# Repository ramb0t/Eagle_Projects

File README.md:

# Eagle_Projects

A Place to keep my older Eagle Projects from Dropbox... Some noob, Most unfinished.

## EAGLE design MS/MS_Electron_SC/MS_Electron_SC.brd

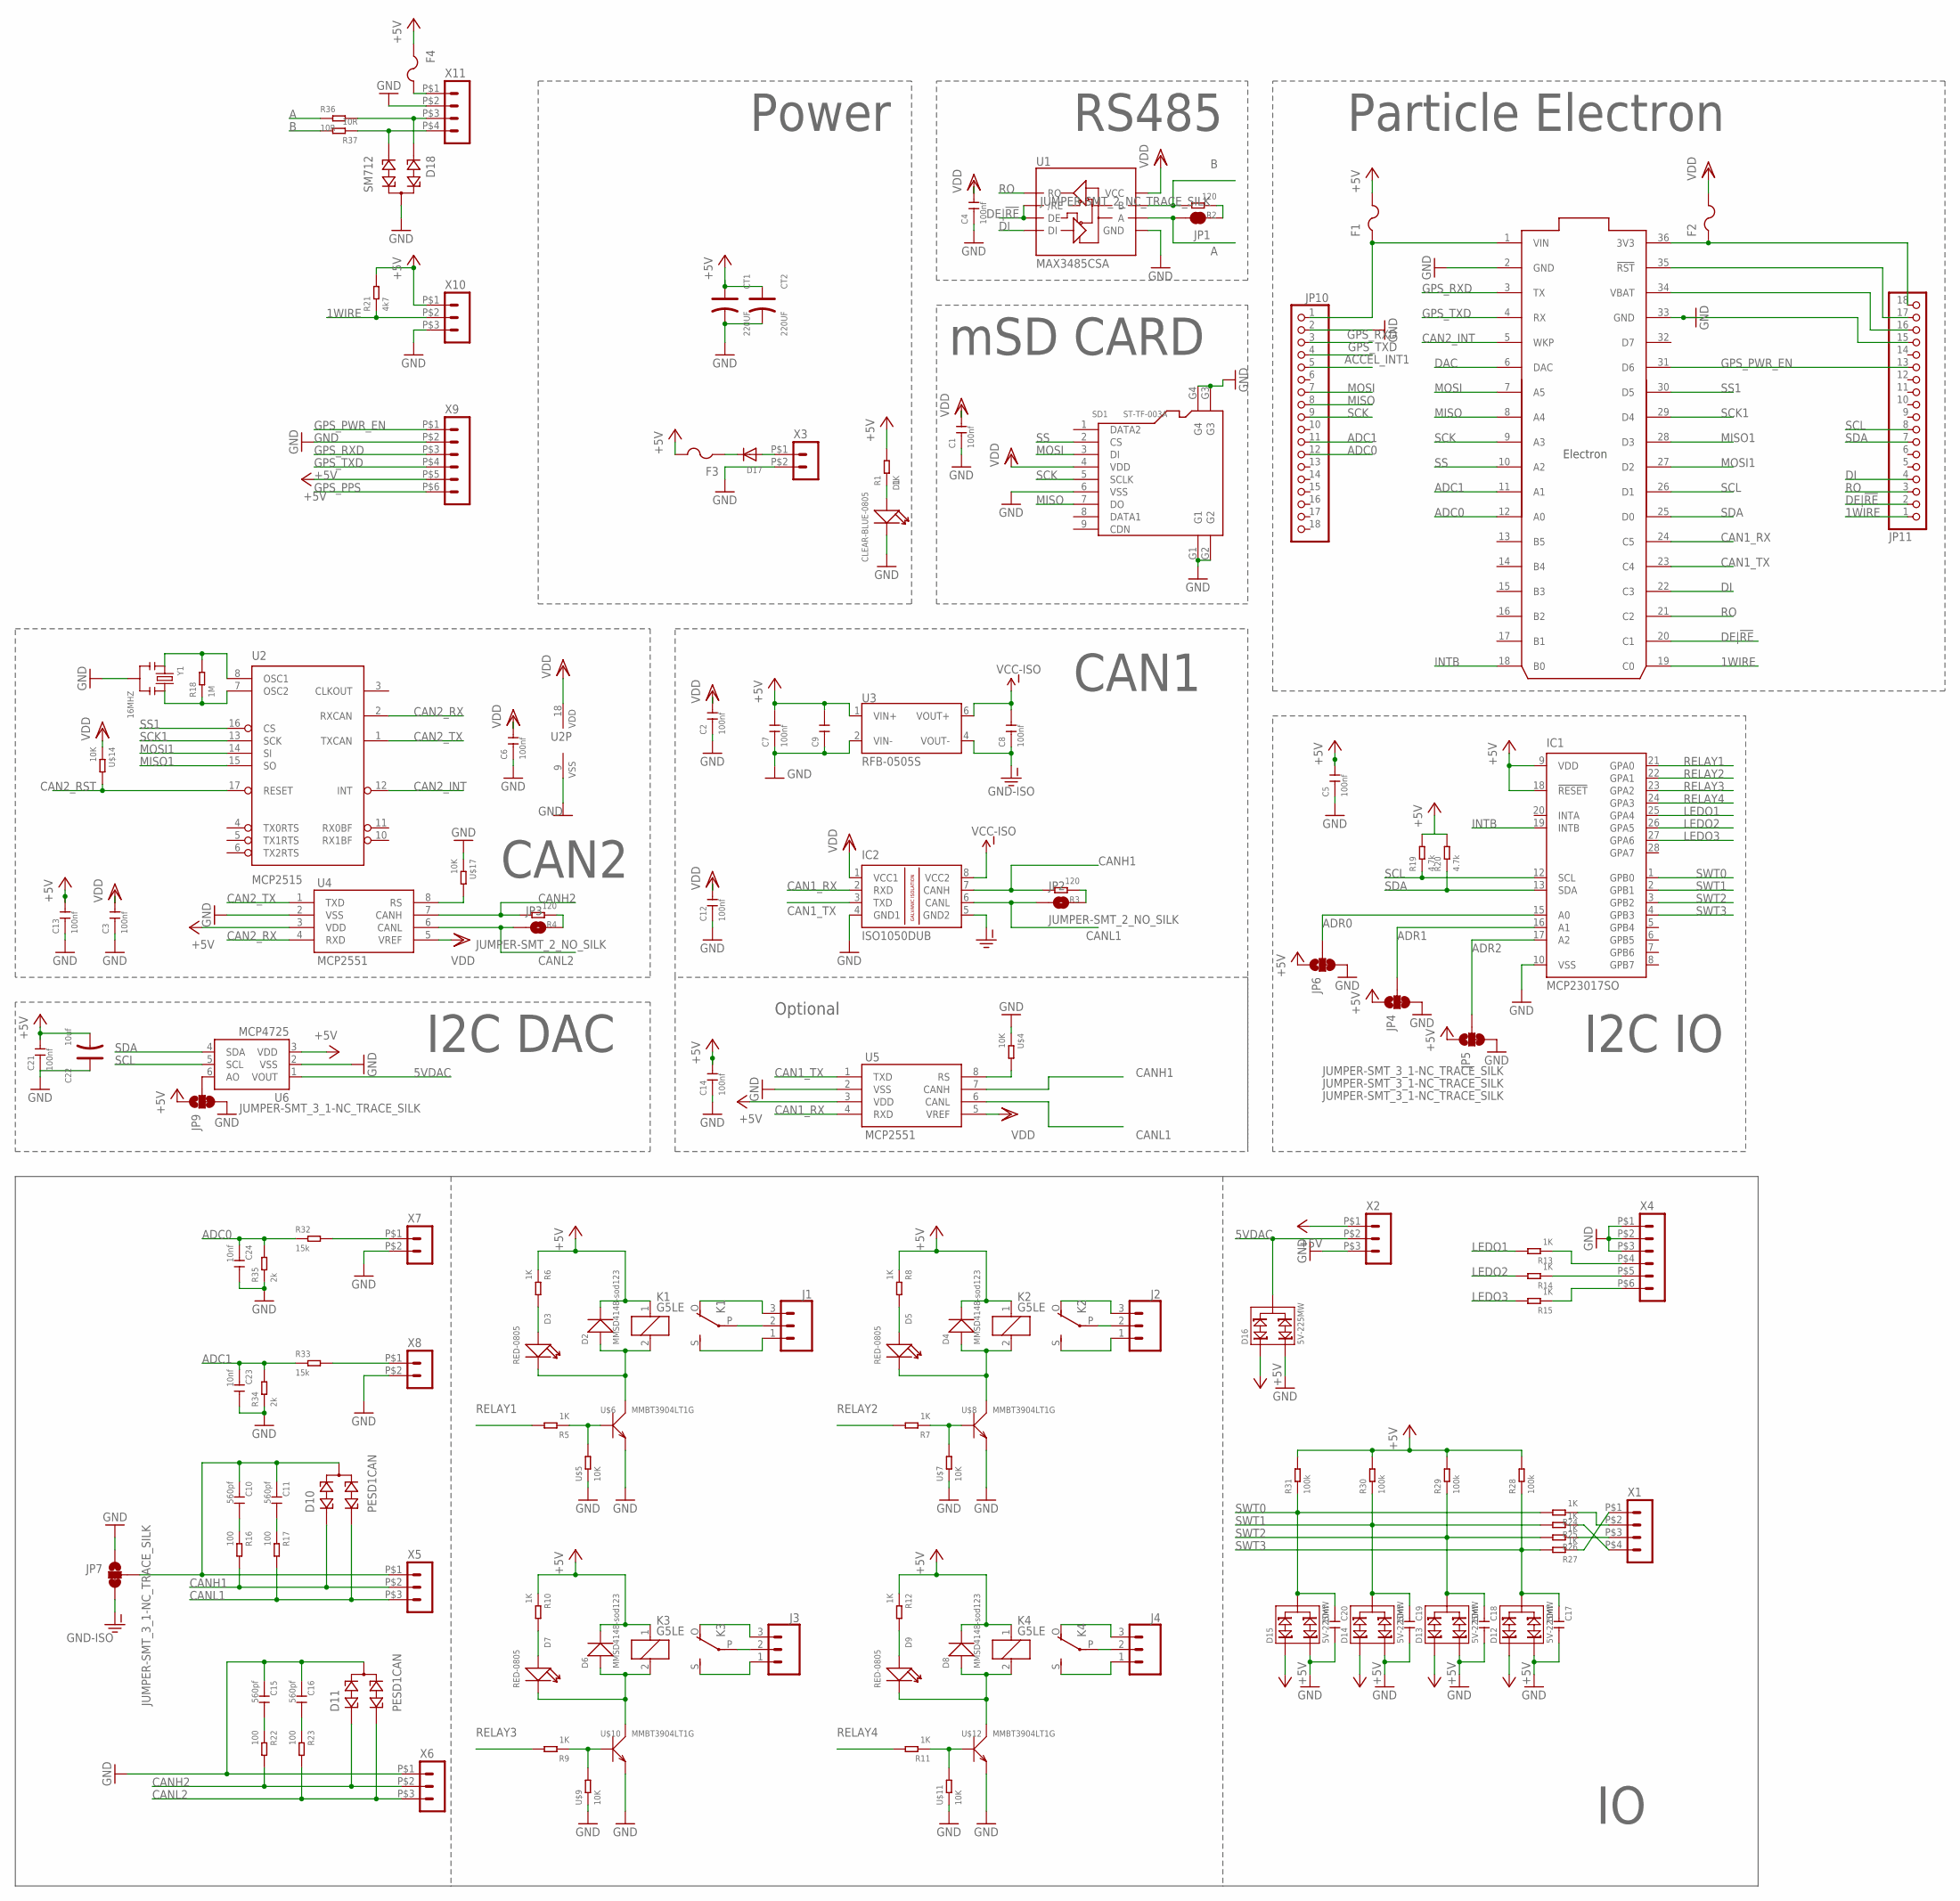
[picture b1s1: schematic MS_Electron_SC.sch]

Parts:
C1, C2, C3, C4, C5, C6, C7, C8, C12, C13, C14, C21: 100nf; C0805
C9: CERAMIC-22UF-16V-10%-X7R(1206); C1206
C10, C11, C15, C16: 560pf; C0805
C17, C18, C19, C20, C23, C24: 10nf; C0805
C22: 10uf; AVX-A
CT1, CT2: 220UF; ELECTRO-SMD-C-6MM
D1: CLEAR-BLUE-0805; LED-0805
D2, D4, D6, D8: MMSD4148-sod123; SOD-123
D3, D5, D7, D9: RED-0805; LED-0805
D10, D11: PESD1CAN; SOT23
D12, D13, D14, D15, D16: 5V-225MW; SOT-23
D17: DIODESMA; SMADIODE
D18: SM712; SOT23
F1, F2, F3, F4: PTCFUSE-1812; 1812
IC1: MCP23017SO; SO28W
IC2: ISO1050DUB; DUB-R-PDSO-G8
J1, J2, J3, J4: CONN_03SCREW; SCREWTERMINAL-3.5MM-3
JP1: JUMPER-SMT_2_NC_TRACE_SILK; SMT-JUMPER_2_NC_TRACE_SILK
JP2, JP3: JUMPER-SMT_2_NO_SILK; SMT-JUMPER_2_NO_SILK
JP4, JP5, JP6, JP7, JP9: JUMPER-SMT_3_1-NC_TRACE_SILK; SMT-JUMPER_3_1-NC_TRACE_SILK
JP10, JP11: PINHD-1X18-BIG; 1X18-BIG
K1, K2, K3, K4: G5LE
R1, R5, R6, R7, R8, R9, R10, R11, R12, R13, R14, R15, R24, R25, R26, R27: 1K; R0805
R2, R3, R4: 120; R0805
R16, R17, R22, R23: 100; R0805
R18: 1M; R0805
R19, R20: 4.7k; R0805
R21: 4k7; R0805
R28, R29, R30, R31: 100k; R0805
R32, R33: 15k; R0805
R34, R35: 2k; R0805
R36, R37: 10R; R0805
SD1: ST-TF-003A; MICRO-SD9+4P-SMD-16.1X14.5X1.85MM
U1: MAX3485CSA; SO08
U2: MCP2515; SO18W
U3: RFB-0505S
U4, U5: MCP2551; SO08
U6: MCP4725; SOT23-6
U$1: ELECTRON_WITH_HEADERS; ELECTRON
U$4, U$5, U$7, U$9, U$11, U$14, U$17: 10K; R0805
U$6, U$8, U$10, U$12: MMBT3904LT1G; SOT-23
X1, X11: HEADER_POS4_43045-0401; 43045-0400
X2, X5, X6, X10: HEADER_POS3_43650-0300; 43650-0300
X3, X7, X8: HEADER_POS2_43650-0200; 43650-0200
X4, X9: HEADER_POS6_43045-0600; 43045-0600
Y1: 16MHZ; X3-SMD-3.6X1.3X0.8MM

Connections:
1WIRE: JP11.1, R21.1, U$1.19 (C0), X10.P$2 (2)
5VDAC: D16.3, U6.1 (VOUT), X2.P$2 (2)
+5V: C5.2, C7.2, C9.2, C13.2, C14.2, C21.2, C22.-, CT1.+, CT2.+, D2.-, D4.-, D6.-, D8.-, D12.1, D13.1, D14.1, D15.1, D16.1, F1.2, F3.2, F4.1, IC1.9 (VDD), IC1.18 (!RESET), JP4.1, JP5.1, JP6.1, JP9.1, K1.1, K2.1, K3.1, K4.1, R1.2, R6.1, R8.1, R10.1, R12.1, R19.2, R20.2, R21.2, R28.2, R29.2, R30.2, R31.2, U3.1 (VIN+), U4.3 (VDD), U5.3 (VDD), U6.3 (VDD), X2.P$1 (1), X9.P$5 (5), X10.P$1 (1)
A: JP1.2, R36.1, U1.6 (A)
ACCEL_INT1: JP10.5
ADC0: C24.1, JP10.12, R32.1, R35.2, U$1.12 (A0)
ADC1: C23.1, JP10.11, R33.1, R34.2, U$1.11 (A1)
ADR0: IC1.15 (A0), JP6.2
ADR1: IC1.16 (A1), JP4.2
ADR2: IC1.17 (A2), JP5.2
B: R2.2, R37.2, U1.7 (B)
CAN1_RX: IC2.2 (RXD), U5.4 (RXD), U$1.24 (C5)
CAN1_TX: IC2.3 (TXD), U5.1 (TXD), U$1.23 (C4)
CAN2_INT: U2.12 (INT), U$1.5 (WKP)
CAN2_RST: U2.17 (RESET), U$14.2
CAN2_RX: U2.2 (RXCAN), U4.4 (RXD)
CAN2_TX: U2.1 (TXCAN), U4.1 (TXD)
CANH1: D10.1, IC2.7 (CANH), R3.2, R16.2, U5.7 (CANH), X5.P$2 (2)
CANH2: D11.1, R4.2, R22.2, U4.7 (CANH), X6.P$2 (2)
CANL1: D10.2, IC2.6 (CANL), JP2.1, R17.2, U5.6 (CANL), X5.P$3 (3)
CANL2: D11.2, JP3.1, R23.2, U4.6 (CANL), X6.P$3 (3)
DAC: U$1.6 (DAC)
DE|!RE: JP11.2, U1.2 (/RE), U1.3 (DE), U$1.20 (C1)
DI: JP11.4, U1.4 (DI), U$1.22 (C3)
GND: C1.1, C2.1, C3.1, C4.1, C5.1, C6.1, C7.1, C9.1, C12.1, C13.1, C14.1, C15.1, C16.1, C17.2, C18.2, C19.2, C20.2, C21.1, C22.+, C23.2, C24.2, CT1.-, CT2.-, D1.-, D11.3, D12.2, D13.2, D14.2, D15.2, D16.2, D18.3, IC1.10 (VSS), IC2.4 (GND1), JP4.3, JP5.3, JP6.3, JP7.1, JP9.3, JP10.2, JP11.15, R34.1, R35.1, SD1.6 (VSS), SD1.G1, SD1.G2, SD1.G3, SD1.G4, U1.5 (GND), U2.9 (VSS), U3.2 (VIN-), U4.2 (VSS), U5.2 (VSS), U6.2 (VSS), U$1.2 (GND), U$1.33 (GND), U$4.1, U$5.1, U$6.2 (E), U$7.1, U$8.2 (E), U$9.1, U$10.2 (E), U$11.1, U$12.2 (E), U$17.1, X2.P$3 (3), X3.P$2 (2), X4.P$1 (1), X4.P$2 (2), X4.P$3 (3), X6.P$1 (1), X7.P$2 (2), X8.P$2 (2), X9.P$2 (2), X10.P$3 (3), X11.P$2 (2), Y1.2
GND-ISO: C8.1, IC2.5 (GND2), JP7.3, U3.4 (VOUT-)
GPS_PPS: X9.P$6 (6)
GPS_PWR_EN: JP11.13, U$1.31 (D6), X9.P$1 (1)
GPS_RXD: JP10.3, U$1.3 (TX), X9.P$3 (3)
GPS_TXD: JP10.4, U$1.4 (RX), X9.P$4 (4)
INTB: IC1.19 (INTB), U$1.18 (B0)
LEDO1: IC1.25 (GPA4), R13.2
LEDO2: IC1.26 (GPA5), R14.2
LEDO3: IC1.27 (GPA6), R15.2
MISO: JP10.8, SD1.7 (DO), U$1.8 (A4)
MISO1: U2.15 (SO), U$1.28 (D3)
MOSI: JP10.7, SD1.3 (DI), U$1.7 (A5)
MOSI1: U2.14 (SI), U$1.27 (D2)
unnamed: D1.+, R1.1
unnamed: JP2.2, R3.1
unnamed: JP1.1, R2.1
unnamed: JP3.2, R4.1
unnamed: R5.1, U$5.2, U$6.1 (B)
unnamed: D2.+, D3.-, K1.2, U$6.3 (C)
unnamed: D3.+, R6.2
unnamed: J1.2, K1.P
unnamed: J1.3, K1.O
unnamed: J1.1, K1.S
unnamed: D4.+, D5.-, K2.2, U$8.3 (C)
unnamed: R7.1, U$7.2, U$8.1 (B)
unnamed: D5.+, R8.2
unnamed: J3.2, K3.P
unnamed: J2.3, K2.O
unnamed: J2.1, K2.S
unnamed: D6.+, D7.-, K3.2, U$10.3 (C)
unnamed: R9.1, U$9.2, U$10.1 (B)
unnamed: D7.+, R10.2
unnamed: J2.2, K2.P
unnamed: J3.3, K3.O
unnamed: J3.1, K3.S
unnamed: D8.+, D9.-, K4.2, U$12.3 (C)
unnamed: R11.1, U$11.2, U$12.1 (B)
unnamed: D9.+, R12.2
unnamed: J4.2, K4.P
unnamed: J4.3, K4.O
unnamed: J4.1, K4.S
unnamed: R14.1, X4.P$5 (5)
unnamed: R13.1, X4.P$4 (4)
unnamed: R15.1, X4.P$6 (6)
unnamed: F2.1, JP11.18, U$1.36 (3V3)
unnamed: U5.8 (RS), U$4.2
unnamed: C11.2, R17.1
unnamed: C10.2, R16.1
unnamed: R18.1, U2.7 (OSC2), Y1.3
unnamed: R18.2, U2.8 (OSC1), Y1.1
unnamed: C10.1, C11.1, D10.3, JP7.2, X5.P$1 (1)
unnamed: C16.2, R23.1
unnamed: U4.8 (RS), U$17.2
unnamed: C15.2, R22.1
unnamed: R24.1, X1.P$2 (2)
unnamed: R27.1, X1.P$1 (1)
unnamed: R25.1, X1.P$4 (4)
unnamed: R26.1, X1.P$3 (3)
unnamed: JP9.2, U6.6 (AO)
unnamed: R33.2, X8.P$1 (1)
unnamed: R32.2, X7.P$1 (1)
unnamed: JP11.17, U$1.35 (!RST)
unnamed: JP11.16, U$1.34 (VBAT)
unnamed: F1.1, JP10.1, U$1.1 (VIN)
unnamed: D17.A, X3.P$1 (1)
unnamed: D17.C, F3.1
unnamed: D18.1, R36.2, X11.P$3 (3)
unnamed: D18.2, R37.1, X11.P$4 (4)
unnamed: F4.2, X11.P$1 (1)
RELAY1: IC1.21 (GPA0), R5.2
RELAY2: IC1.22 (GPA1), R7.2
RELAY3: IC1.23 (GPA2), R9.2
RELAY4: IC1.24 (GPA3), R11.2
RO: JP11.3, U1.1 (RO), U$1.21 (C2)
SCK: JP10.9, SD1.5 (SCLK), U$1.9 (A3)
SCK1: U2.13 (SCK), U$1.29 (D4)
SCL: IC1.12 (SCL), JP11.8, R19.1, U6.5 (SCL), U$1.26 (D1)
SDA: IC1.13 (SDA), JP11.7, R20.1, U6.4 (SDA), U$1.25 (D0)
SS: SD1.2 (CS), U$1.10 (A2)
SS1: U2.16 (CS), U$1.30 (D5)
SWT0: C20.1, D15.3, IC1.1 (GPB0), R24.2, R31.1
SWT1: C19.1, D14.3, IC1.2 (GPB1), R25.2, R30.1
SWT2: C18.1, D13.3, IC1.3 (GPB2), R26.2, R29.1
SWT3: C17.1, D12.3, IC1.4 (GPB3), R27.2, R28.1
VCC-ISO: C8.2, IC2.8 (VCC2), U3.6 (VOUT+)
VDD: C1.2, C2.2, C3.2, C4.2, C6.2, C12.2, F2.2, IC2.1 (VCC1), SD1.4 (VDD), U1.8 (VCC), U2.18 (VDD), U4.5 (VREF), U5.5 (VREF), U$14.1

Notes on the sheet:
CAN2
CAN1
Optional
I2C IO
I2C DAC
Particle Electron
mSD CARD
RS485
Power

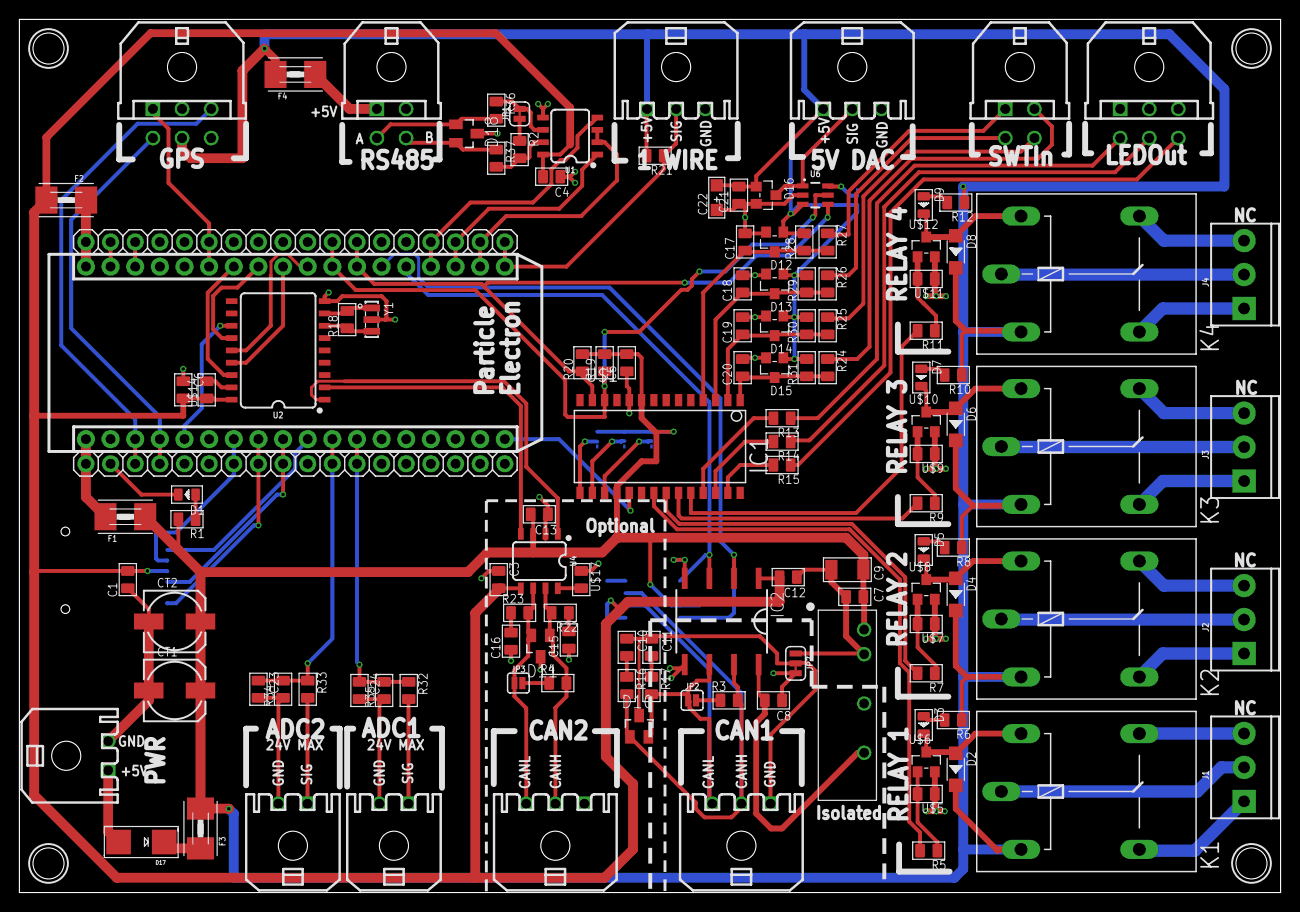
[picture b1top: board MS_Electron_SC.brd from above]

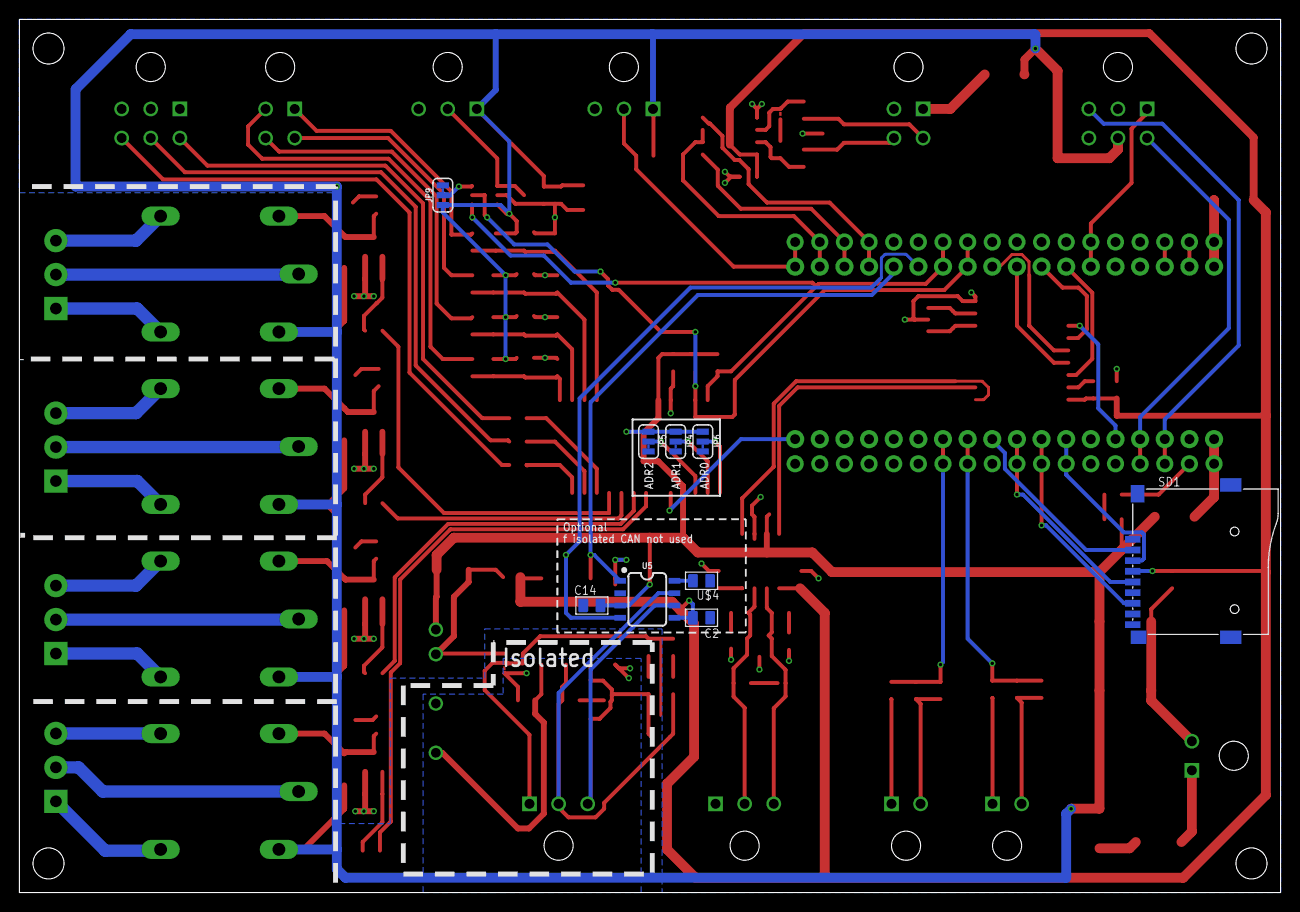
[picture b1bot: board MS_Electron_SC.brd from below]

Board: 4 copper layers, 130.0 x 90.0 mm, 136 parts (9 on the bottom side), 108 nets.

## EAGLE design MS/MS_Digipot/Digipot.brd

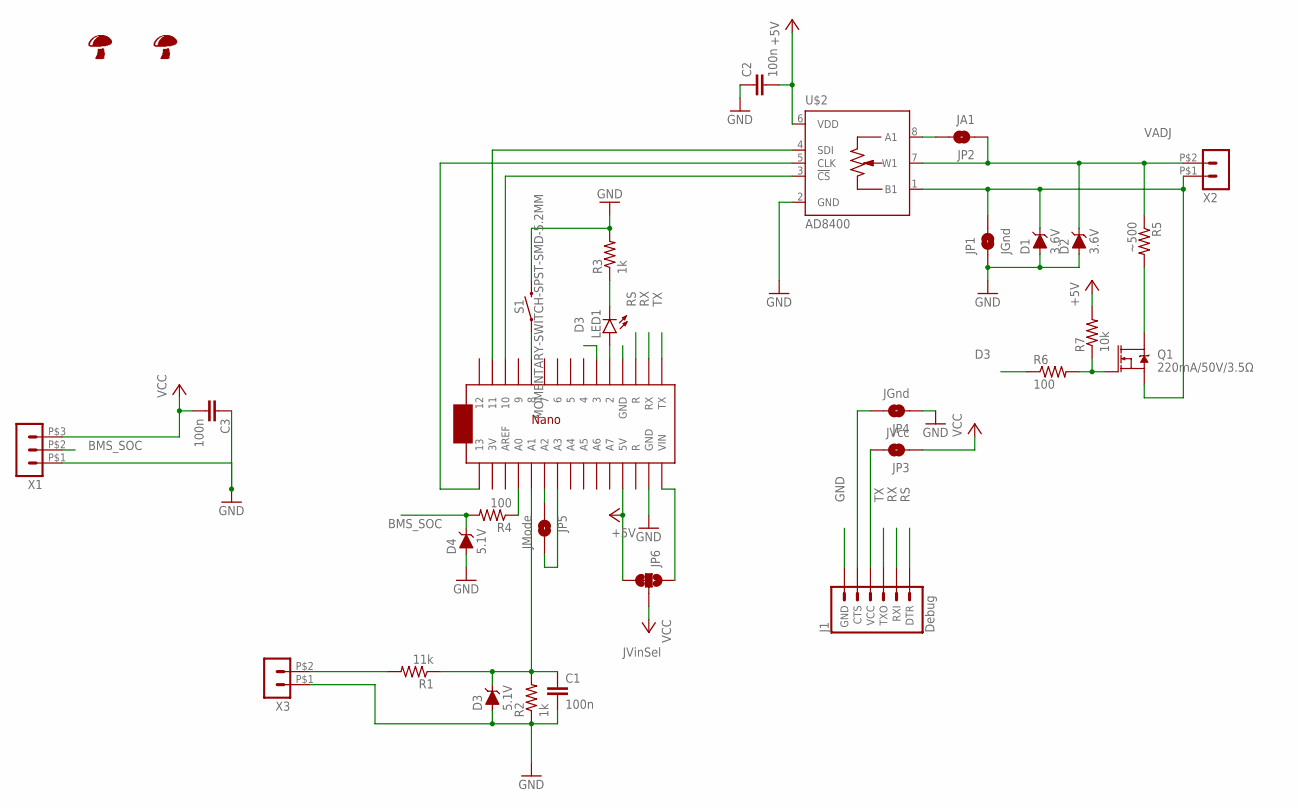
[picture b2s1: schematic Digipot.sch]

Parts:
C1, C2, C3: 100n; C0805
D1, D2: 3.6V; SOD-323
D3, D4: 5.1V; SOD-323
J1: Debug; 1X06_LOCK
JP1, JP4: JGnd; SMT-JUMPER_2_NO_SILK
JP2: JA1; SMT-JUMPER_2_NO_SILK
JP3: JVcc; SMT-JUMPER_2_NO_SILK
JP5: JMode; SMT-JUMPER_2_NO_SILK
JP6: JVinSel; SMT-JUMPER_3_1-NC_TRACE_SILK
LED1: LEDCHIPLED_0805; CHIPLED_0805
Q1: 220mA/50V/3.5Ω; SOT23-3
R1: 11k; R0805
R2, R3: 1k; R0805
R4, R6: 100; R0805
R5: ~500; R0805
R7: 10k; R0805
S1: MOMENTARY-SWITCH-SPST-SMD-5.2MM; TACTILE_SWITCH_SMD_5.2MM
U$1: ARDUINO_NANOARDUINONANO; ARDUINOMICRO
U$2: AD8400; SOIC08
U$3: SHROOMTOPSILK; SHROOM_TS
U$4: SHROOM5MM; SHROOM
X1: HEADER_POS3_43650-0300; 43650-0300
X2, X3: HEADER_POS2_43650-0200; 43650-0200

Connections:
+5V: C2.2, JP6.3, R7.2, U$1.P$23 (5V), U$2.6 (VDD)
BMS_SOC: D4.C, R4.2, X1.P$2 (2)
D3: R6.1, U$1.P$10 (3)
GND: C1.2, C2.1, C3.1, D1.A, D2.A, D3.A, D4.A, J1.6 (GND), JP1.1, JP4.1, R2.1, R3.2, S1.3 (2), U$1.P$12 (GND), U$1.P$21 (GND), U$2.2 (GND), X1.P$1 (1), X3.P$1 (1)
unnamed: C1.1, D3.C, R1.1, R2.2, U$1.P$30 (A1)
unnamed: R1.2, X3.P$2 (2)
unnamed: D1.C, JP1.2, Q1.2 (S), U$2.1 (B1), X2.P$1 (1)
unnamed: U$1.P$3 (10), U$2.3 (!CS)
unnamed: U$1.P$2 (11), U$2.4 (SDI)
unnamed: U$1.P$34 (13), U$2.5 (CLK)
unnamed: J1.4 (VCC), JP3.2
unnamed: JP2.2, U$2.8 (A1)
unnamed: J1.5 (CTS), JP4.2
unnamed: LED1.C, R3.1
unnamed: LED1.A, U$1.P$11 (2)
unnamed: R4.1, U$1.P$31 (A0)
unnamed: JP5.1, U$1.P$29 (A2)
unnamed: JP5.2, U$1.P$28 (A3)
unnamed: JP6.1, U$1.P$20 (VIN)
unnamed: Q1.3 (D), R5.2
unnamed: Q1.1 (G), R6.2, R7.1
unnamed: S1.1, U$1.P$5 (8)
RS: J1.1 (DTR), U$1.P$22 (R)
RX: J1.2 (RXI), U$1.P$14 (RX)
TX: J1.3 (TXO), U$1.P$15 (TX)
VADJ: D2.C, JP2.1, R5.1, U$2.7 (W1), X2.P$2 (2)
VCC: C3.2, JP3.1, JP6.2, X1.P$3 (3)

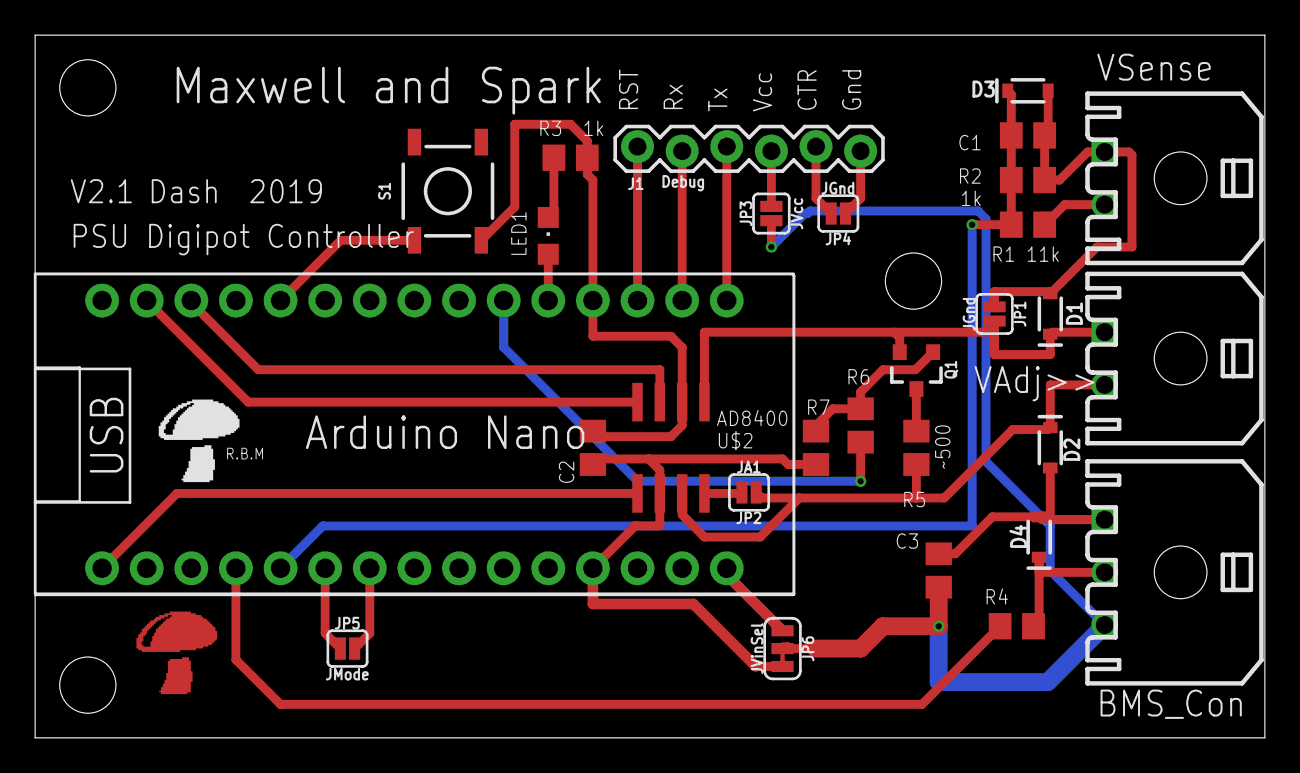
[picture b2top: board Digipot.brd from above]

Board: 2 copper layers, 70.0 x 40.0 mm, 31 parts (0 on the bottom side), 27 nets.

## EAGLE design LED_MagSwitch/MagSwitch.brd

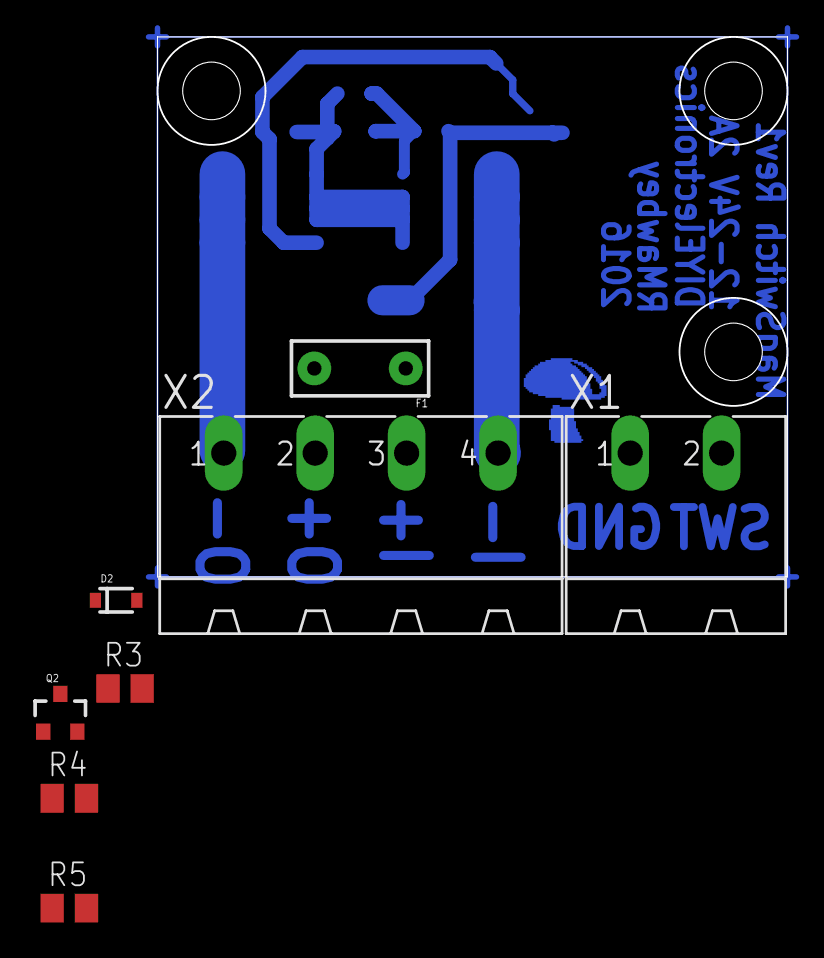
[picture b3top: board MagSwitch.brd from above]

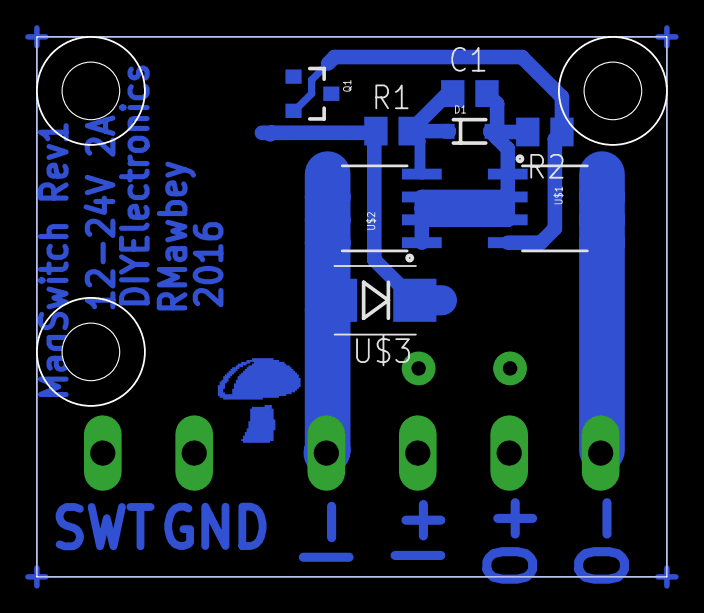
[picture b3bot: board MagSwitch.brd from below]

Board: 2 copper layers, 35.0 x 30.0 mm, 17 parts (9 on the bottom side), 10 nets.

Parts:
C1: 100nF; C0805
D1: DIODE-ZENER15V; SOD-323
D2: DIODE-ZENER8V; SOD-323
F1: PTCPTH; PTC
Q1, Q2: MMBT2222A; SOT23-3
R1: 5k6; M0805
R2, R3: 10k; M0805
R4, R5: 4k7; M0805
U$1, U$2: DMG4466SSS; SO08
U$3: DIODE_TVS_BISM6T30CAY; SMB-DIODE
U$4: SHROOM5MM; SHROOM
X1: MSTBA2
X2: MSTBA4

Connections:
+24V: D2.C, R1.1, R5.2, U$3.C, X2.2, X2.3
GND: U$2.5, U$2.6, U$2.7, U$2.8, U$3.A, X2.4
unnamed: D2.A, R3.1, R4.1
unnamed: Q1.1, R4.2
unnamed: C1.2, D1.A, Q1.2, Q2.2, R2.2, R3.2, U$1.1, U$1.2, U$1.3, U$2.1, U$2.2, U$2.3
unnamed: R2.1, U$1.4, X1.1
unnamed: F1.P$2, X2.1
unnamed: C1.1, D1.C, Q2.3, R1.2, U$2.4, X1.2
unnamed: Q1.3, Q2.1, R5.1
OUT-: F1.P$1, U$1.5, U$1.6, U$1.7, U$1.8

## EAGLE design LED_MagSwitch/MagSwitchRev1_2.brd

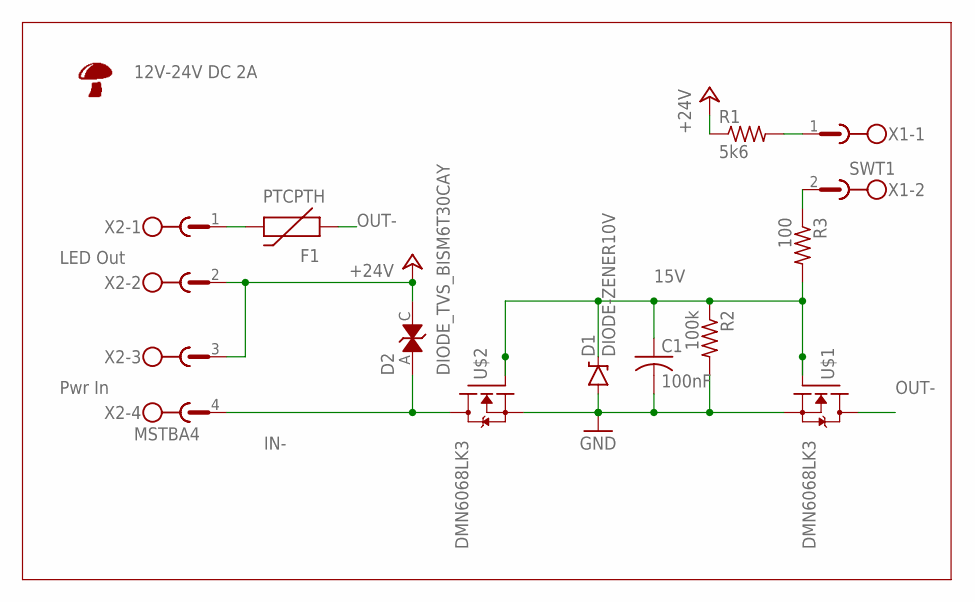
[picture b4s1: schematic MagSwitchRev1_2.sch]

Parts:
C1: 100nF; C0805
D1: DIODE-ZENER10V; SOD-323
D2: DIODE_TVS_BISM6T30CAY; SMB-DIODE
F1: PTCPTH; PTC
R1: 5k6; M0805
R2: 100k; M0805
R3: 100; M0805
U$1, U$2: DMN6068LK3; TO252
U$4: SHROOM5MM; SHROOM
X1: SWT1; MSTBA2
X2: MSTBA4

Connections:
15V: C1.1, D1.C, R2.1, R3.2, U$1.1 (G), U$2.1 (G)
+24V: D2.C, R1.1, X2.2, X2.3
GND: C1.2, D1.A, R2.2, U$1.2 (S), U$2.2 (S)
IN-: D2.A, U$2.3 (D), X2.4
unnamed: F1.P$2 (2), X2.1
unnamed: R1.2, X1.1
unnamed: R3.1, X1.2
OUT-: F1.P$1 (1), U$1.3 (D)

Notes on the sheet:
Pwr In
LED Out
12V-24V DC 2A

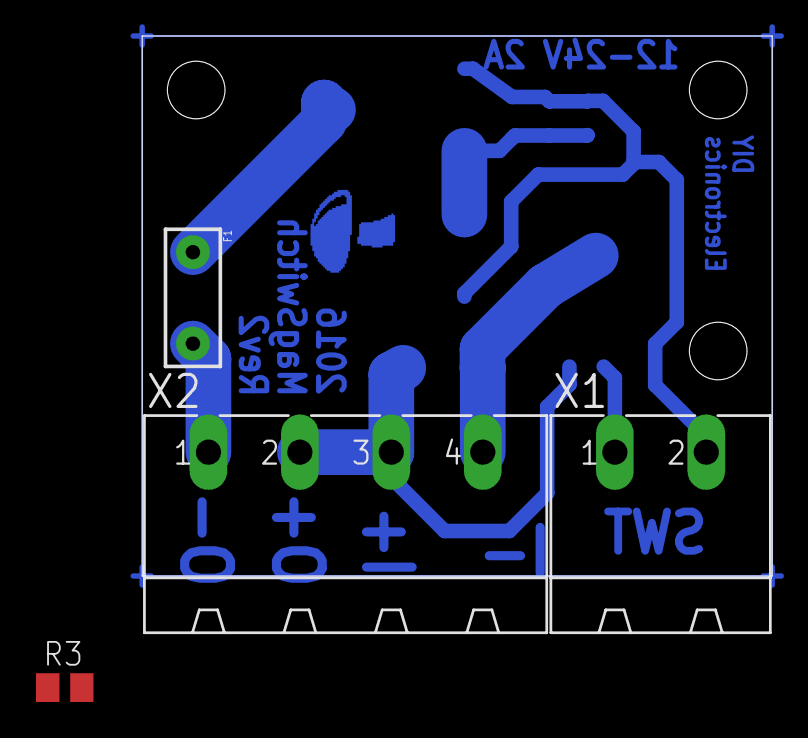
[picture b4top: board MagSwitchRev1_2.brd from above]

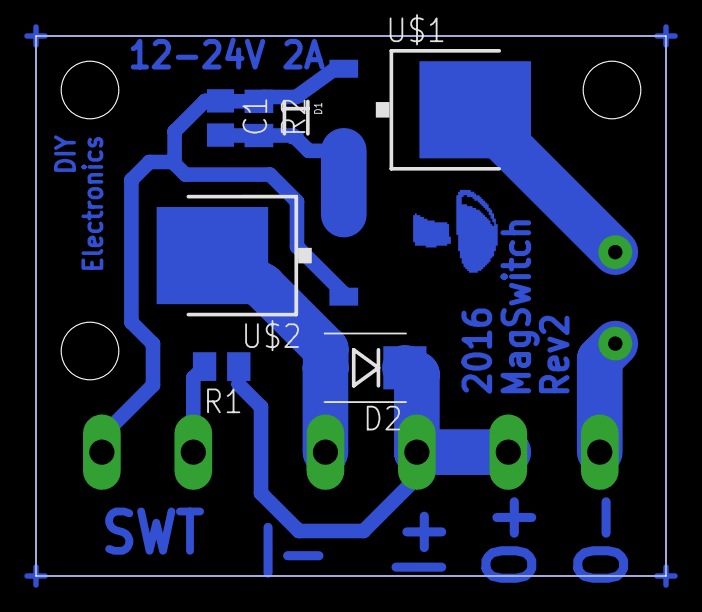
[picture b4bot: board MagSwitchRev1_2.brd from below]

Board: 2 copper layers, 35.0 x 30.0 mm, 12 parts (8 on the bottom side), 8 nets.

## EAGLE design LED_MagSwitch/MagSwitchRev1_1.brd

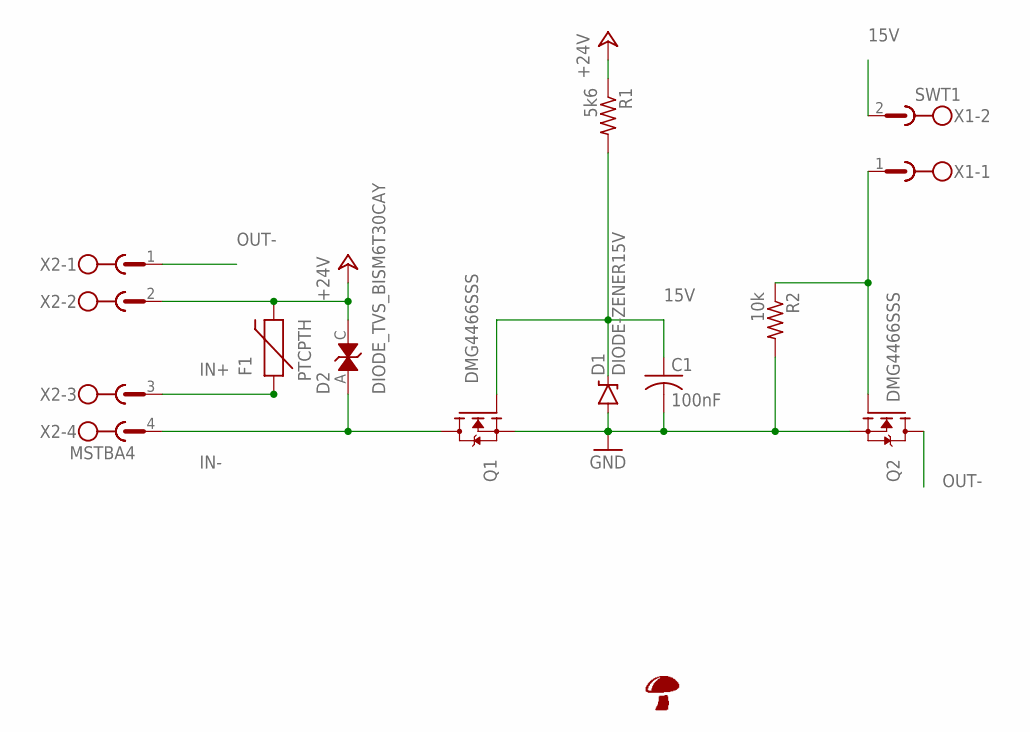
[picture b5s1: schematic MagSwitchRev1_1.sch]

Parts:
C1: 100nF; C0805
D1: DIODE-ZENER15V; SOD-323
D2: DIODE_TVS_BISM6T30CAY; SMB-DIODE
F1: PTCPTH; PTC
Q1, Q2: DMG4466SSS; SO08
R1: 5k6; M0805
R2: 10k; M0805
U$4: SHROOM5MM; SHROOM
X1: SWT1; MSTBA2
X2: MSTBA4

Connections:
15V: C1.1, D1.C, Q1.4 (G), R1.2, X1.2
+24V: D2.C, F1.P$2 (2), R1.1, X2.2
GND: C1.2, D1.A, Q1.1 (S), Q1.2 (S), Q1.3 (S), Q2.1 (S), Q2.2 (S), Q2.3 (S), R2.2
IN+: F1.P$1 (1), X2.3
IN-: D2.A, Q1.5 (D), Q1.6 (D), Q1.7 (D), Q1.8 (D), X2.4
unnamed: Q2.4 (G), R2.1, X1.1
OUT-: Q2.5 (D), Q2.6 (D), Q2.7 (D), Q2.8 (D), X2.1

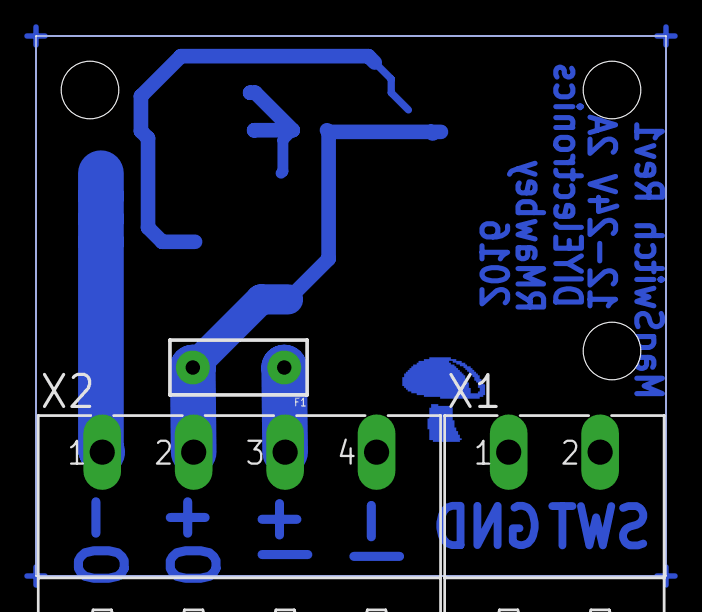
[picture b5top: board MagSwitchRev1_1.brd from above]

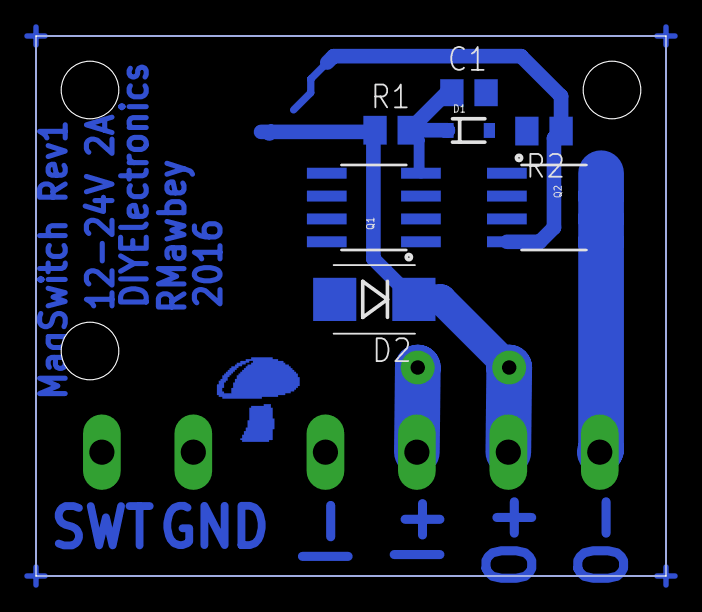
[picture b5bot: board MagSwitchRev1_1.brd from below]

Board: 2 copper layers, 35.0 x 30.0 mm, 11 parts (8 on the bottom side), 7 nets.

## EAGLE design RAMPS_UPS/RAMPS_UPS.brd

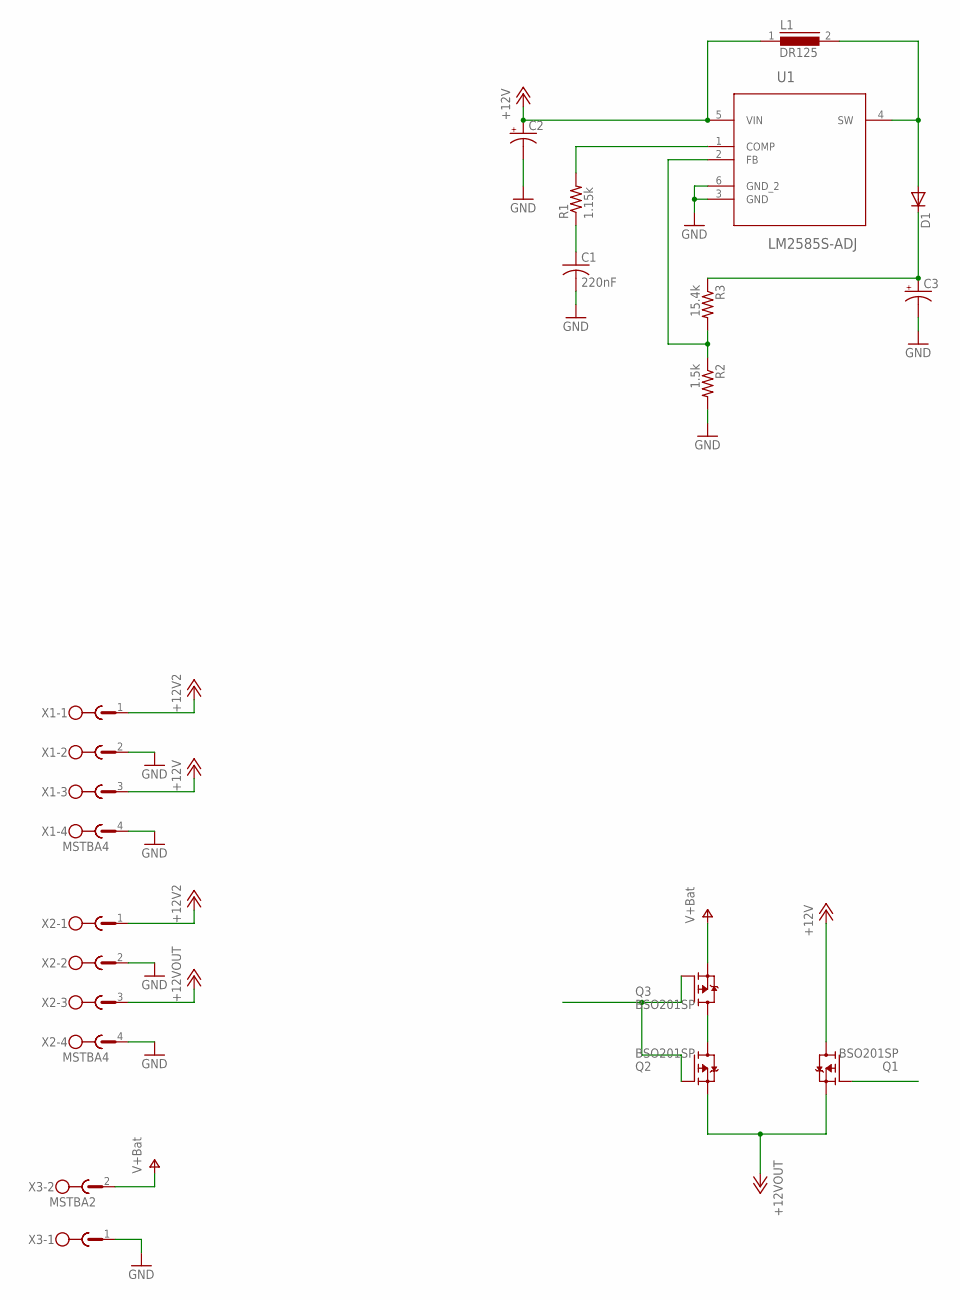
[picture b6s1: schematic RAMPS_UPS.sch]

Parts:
C1: 220nF; C0805K
C2: CPOL-USC; PANASONIC_C
C3: CPOL-USG; PANASONIC_G
D1: DIODE-SMB; SMB
L1: DR125
Q1, Q2, Q3: BSO201SP; SO-8
R1: 1.15k; R0805
R2: 1.5k; R0805
R3: 15.4k; R0805
U1: LM2585S-ADJ; TO170P1435X457-5N
X1, X2: MSTBA4
X3: MSTBA2

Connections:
+12V: C2.+, L1.1, U1.5 (VIN)
+12V1: Q1.5 (D), Q1.6 (D), Q1.7 (D), Q1.8 (D), X1.3
+12V2: X1.1, X2.1
+12VOUT: Q1.1 (S), Q1.2 (S), Q1.3 (S), Q2.1 (S), Q2.2 (S), Q2.3 (S), X2.3
GND: C1.2, C2.-, C3.-, R2.2, U1.3 (GND), U1.6 (GND_2), X1.2, X1.4, X2.2, X2.4, X3.1
unnamed: Q2.5 (D), Q2.6 (D), Q2.7 (D), Q2.8 (D), Q3.5 (D), Q3.6 (D), Q3.7 (D), Q3.8 (D)
unnamed: R2.1, R3.2, U1.2 (FB)
unnamed: R1.2, U1.1 (COMP)
unnamed: C1.1, R1.1
unnamed: Q2.4 (G), Q3.4 (G)
unnamed: D1.A, L1.2, U1.4 (SW)
unnamed: C3.+, D1.C
V+: Q3.1 (S), Q3.2 (S), Q3.3 (S), X3.2

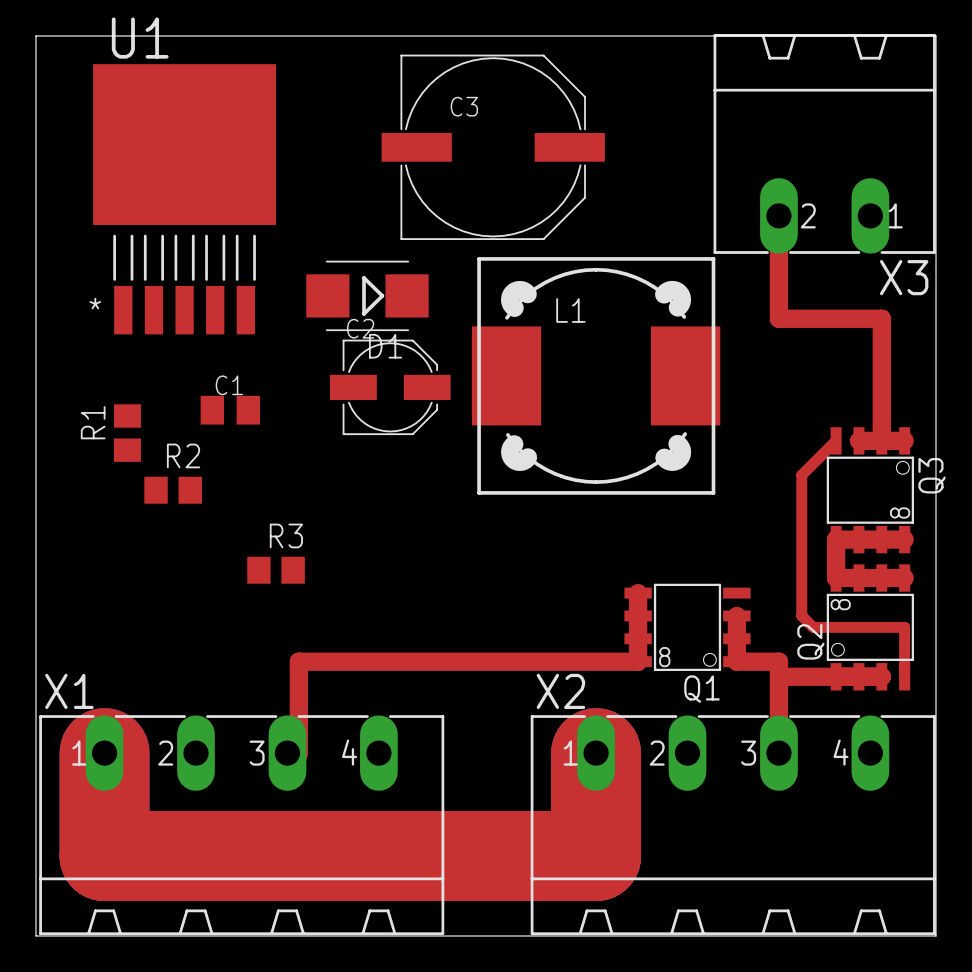
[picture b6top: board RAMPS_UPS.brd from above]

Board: 2 copper layers, 50.0 x 50.0 mm, 15 parts (0 on the bottom side), 13 nets.

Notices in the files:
parts and their libraries:
SparkFun-PowerIC: Licensing: Creative Commons ShareAlike 4.0 International - https://creativecommons.org/licenses/by-sa/4.0
Particle-Devices: Licensing: Designed by Particle.
